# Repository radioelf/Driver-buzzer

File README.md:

# Driver-buzzer
PCB driver buzzer inverter-non inverter signal (Kicad)

Creative Commons License Disclaimer

UNLESS OTHERWISE MUTUALLY AGREED TO BY THE PARTIES IN WRITING, LICENSOR OFFERS THE WORK AS-IS AND MAKES NO REPRESENTATIONS OR WARRANTIES OF ANY KIND CONCERNING THE WORK, EXPRESS, IMPLIED, STATUTORY OR OTHERWISE, INCLUDING, WITHOUT LIMITATION, WARRANTIES OF TITLE, MERCHANTIBILITY, FITNESS FOR A PARTICULAR PURPOSE, NONINFRINGEMENT, OR THE ABSENCE OF LATENT OR OTHER DEFECTS, ACCURACY, OR THE PRESENCE OF ABSENCE OF ERRORS, WHETHER OR NOT DISCOVERABLE. SOME JURISDICTIONS DO NOT ALLOW THE EXCLUSION OF IMPLIED WARRANTIES, SO SUCH EXCLUSION MAY NOT APPLY TO YOU. EXCEPT TO THE EXTENT REQUIRED BY APPLICABLE LAW, IN NO EVENT WILL LICENSOR BE LIABLE TO YOU ON ANY LEGAL THEORY FOR ANY SPECIAL, INCIDENTAL, CONSEQUENTIAL, PUNITIVE OR EXEMPLARY DAMAGES ARISING OUT OF THIS LICENSE OR THE USE OF THE WORK, EVEN IF LICENSOR HAS BEEN ADVISED OF THE POSSIBILITY OF SUCH DAMAGES.

http://creativecommons.org/licenses/by-sa/3.0/

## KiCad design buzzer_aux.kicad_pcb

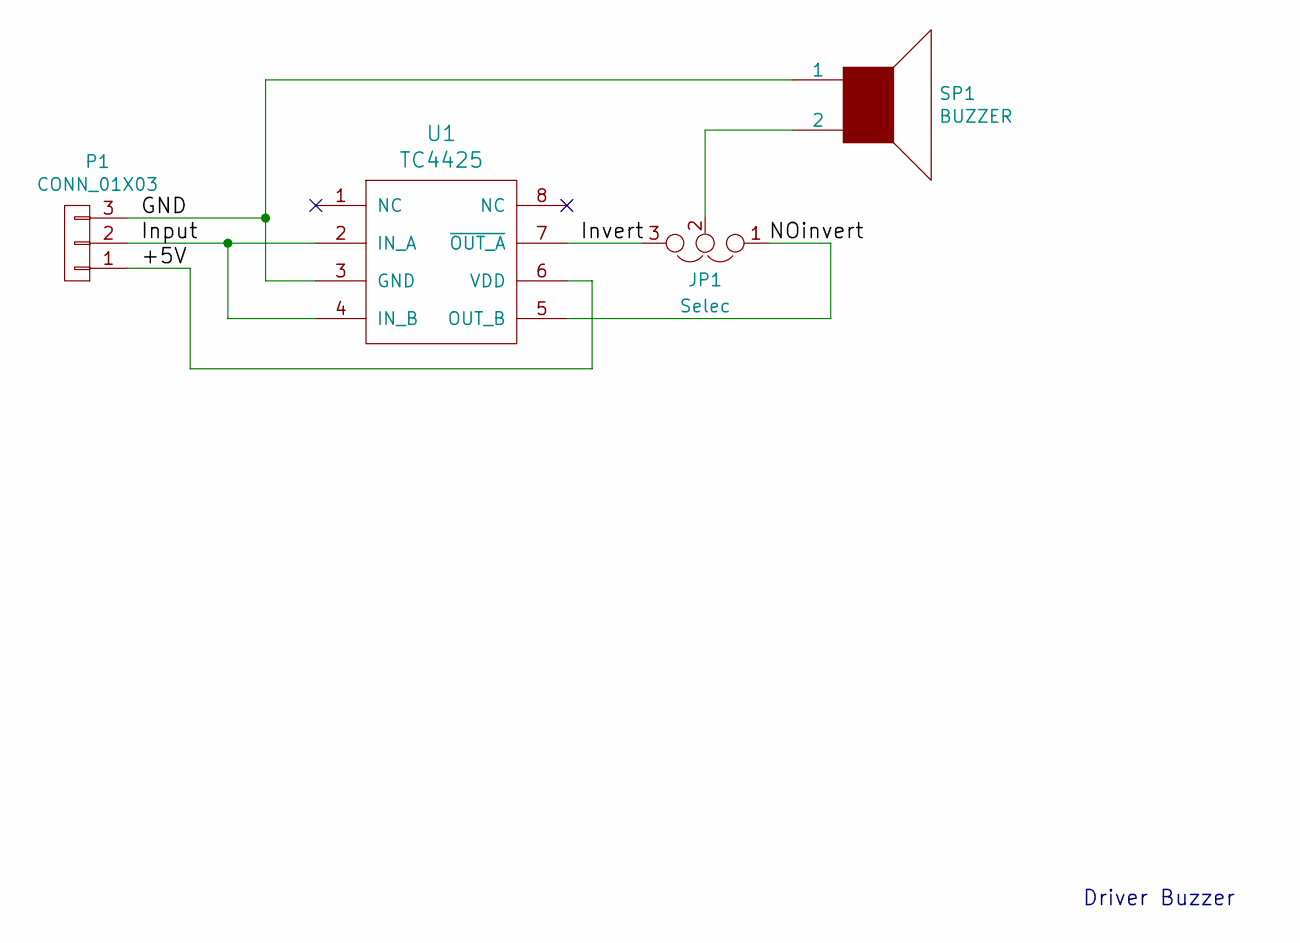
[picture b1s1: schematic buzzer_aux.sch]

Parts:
JP1: Selec; GS3
P1: CONN_01X03; PINHEAD1-3
SP1: BUZZER; MagneticBuzzer_ProSignal_ABI-009-RC
U1: TC4425; SOIC-8-N

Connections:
/+5V: P1.1, U1.6 (VDD)
/GND: P1.3, SP1.1, U1.3 (GND)
/Input: P1.2, U1.2 (IN_A), U1.4 (IN_B)
/Invert: JP1.3, U1.7 (~OUT_A)
/NOinvert: JP1.1, U1.5 (OUT_B)
unnamed: JP1.2, SP1.2

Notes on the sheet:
Driver Buzzer

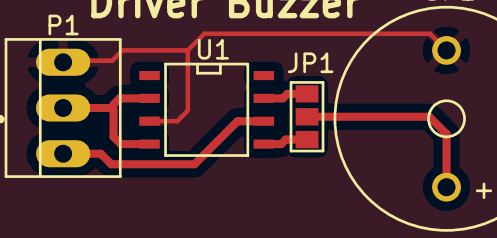
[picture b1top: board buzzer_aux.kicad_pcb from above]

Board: 2 copper layers, 4 parts (0 on the bottom side), 6 nets.

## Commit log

2016-11-14 Files Kicad
